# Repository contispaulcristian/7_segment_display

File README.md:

# 4 Digit 7 Segment Display
### This project features a custom [ATmega328P microcontroller](https://www.microchip.com/en-us/product/atmega328p) board programmed in C. It drives a 4-digit 7-segment display to implement a simple counter application.
####

</br>
Features:

*   Incremental Counter: Displays an incrementing value (0–9999) on the 4-digit 7-segment display.
*   Reset Control: Button resets the microcontroller and the counter to 0.
</br>
Hardware Design:

*   [KiCad](https://www.kicad.org/download/windows/) Schematic: Includes the schematic for easy replication.
*   Can be built on a breadboard, perfboard, or custom PCB.
</br>

</br>

*   Display pinout
</br>

</br>

Programming the Board:
*   For detailed instructions on how to program the ATmega328P microcontroller for this project (including fuse configuration and flashing the hex file), please refer to the programming guide in my other [repository](https://github.com/contispaulcristian/Custom_Board_LED_Patterns).
</br>
Software Details:

*   Multiplexing: The 4-digit 7-segment display is controlled using multiplexing for efficient pin usage.
*   Timer Interrupt: The counter increments every second using a timer interrupt.
</br>
This project demonstrates the use of multiplexed displays, timer interrupts, and basic button controls in embedded systems.

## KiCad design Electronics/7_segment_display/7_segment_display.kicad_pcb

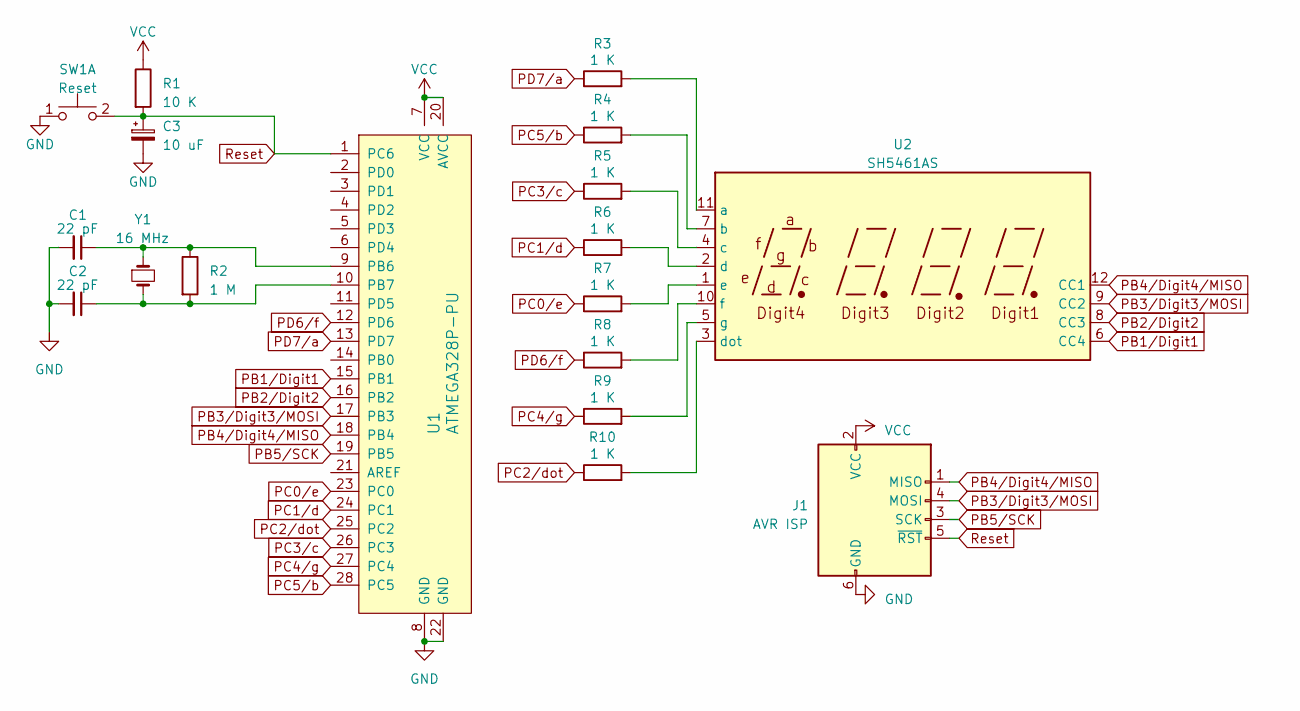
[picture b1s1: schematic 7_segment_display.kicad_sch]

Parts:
C1, C2: 22 pF; C_Disc_D3.0mm_W1.6mm_P2.50mm
C3: 10 uF; CP_Radial_D4.0mm_P1.50mm
J1: AVR ISP; PinHeader_2x03_P2.54mm_Vertical
R1: 10 K; R_Axial_DIN0207_L6.3mm_D2.5mm_P7.62mm_Horizontal
R2: 1 M; R_Axial_DIN0207_L6.3mm_D2.5mm_P7.62mm_Horizontal
R3, R4, R5, R6, R7, R8, R9, R10: 1 K; R_Axial_DIN0207_L6.3mm_D2.5mm_P7.62mm_Horizontal
SW1: Reset; SW_PUSH_6mm_H5mm
U1: ATMEGA328P-PU; DIP-28_W7.62mm; MPN ATMEGA328P-PU; Digi-Key_PN ATMEGA328P-PU-ND
U2: SH5461AS; CA56-12SRWA
Y1: 16 MHz; Crystal_HC49-4H_Vertical

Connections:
GND: C1.2, C2.2, C3.2, J1.6 (GND), SW1.1 (C), U1.8 (GND), U1.22 (GND)
unnamed: C1.1, R2.1, U1.9 (PB6), Y1.1
unnamed: C2.1, R2.2, U1.10 (PB7), Y1.2
unnamed: R3.2, U2.11 (a)
unnamed: R4.2, U2.7 (b)
unnamed: R5.2, U2.4 (c)
unnamed: R6.2, U2.2 (d)
unnamed: R10.2, U2.3 (dot)
unnamed: R7.2, U2.1 (e)
unnamed: R8.2, U2.10 (f)
unnamed: R9.2, U2.5 (g)
PB1/Digit1: U1.15 (PB1), U2.6 (CC4)
PB2/Digit2: U1.16 (PB2), U2.8 (CC3)
PB3/Digit3/MOSI: J1.4 (MOSI), U1.17 (PB3), U2.9 (CC2)
PB4/Digit4/MISO: J1.1 (MISO), U1.18 (PB4), U2.12 (CC1)
PB5/SCK: J1.3 (SCK), U1.19 (PB5)
PC0/e: R7.1, U1.23 (PC0)
PC1/d: R6.1, U1.24 (PC1)
PC2/dot: R10.1, U1.25 (PC2)
PC3/c: R5.1, U1.26 (PC3)
PC4/g: R9.1, U1.27 (PC4)
PC5/b: R4.1, U1.28 (PC5)
PD6/f: R8.1, U1.12 (PD6)
PD7/a: R3.1, U1.13 (PD7)
Reset: C3.1, J1.5 (~RST), R1.2, SW1.2 (D), U1.1 (PC6)
VCC: J1.2 (VCC), R1.1, U1.7 (VCC), U1.20 (AVCC)

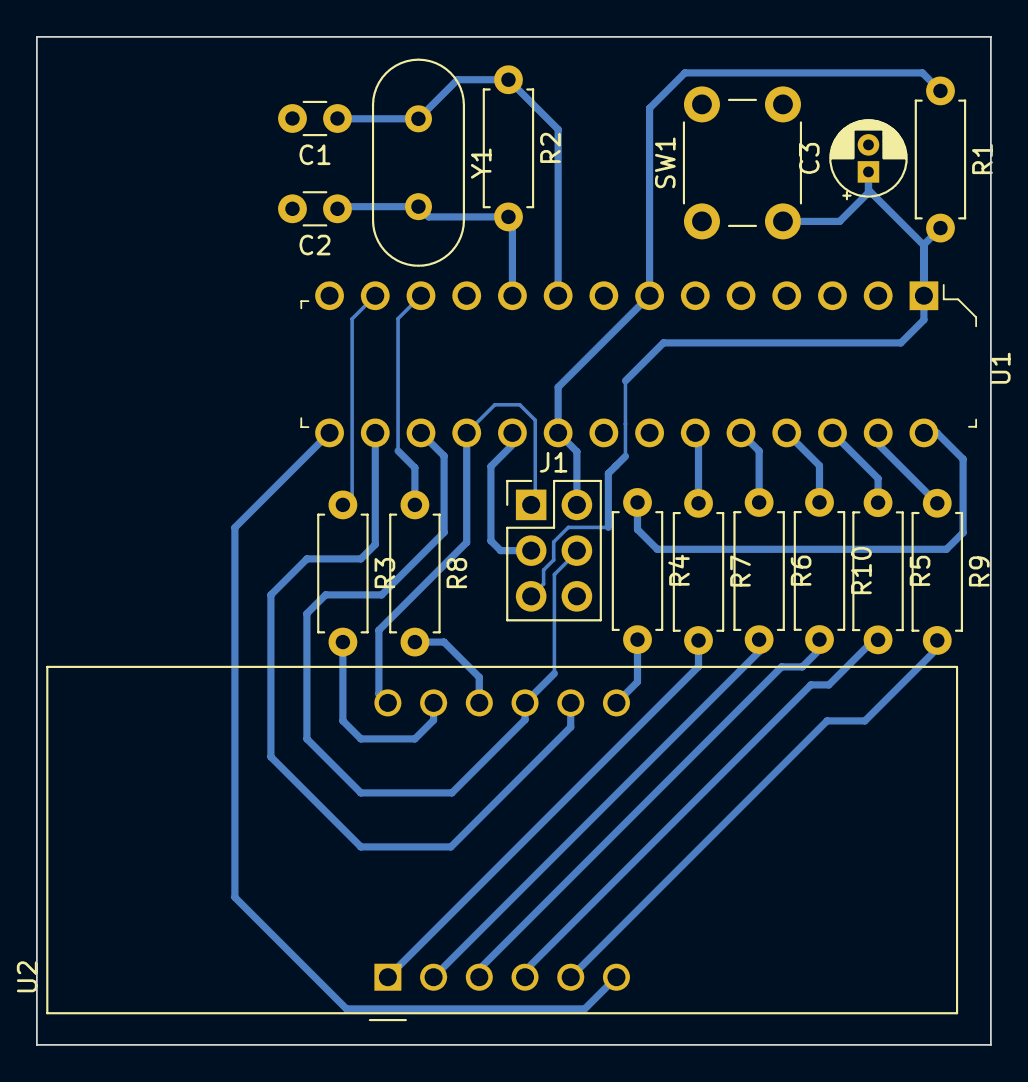
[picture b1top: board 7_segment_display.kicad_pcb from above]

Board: 2 copper layers, 53.0 x 56.0 mm, 18 parts (0 on the bottom side), 26 nets.

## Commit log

2024-12-23 initial empty commit
2024-12-23 empty project
2024-12-23 untested
2025-01-04 kicad project added
2025-01-13 PCB for testing(home made)
2025-01-13 making and demo video
